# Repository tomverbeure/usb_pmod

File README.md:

# USB Combo PMOD

It's common to implement Full Speed or Low Speed (FS/LS) USB host or device controllers
on an FPGA by just using their digital IOs, configured as 3V3 LVCMOS. 

A good example is the [TinyFPGA BX board](https://www.adafruit.com/product/4038), 
which comes by default with a hardware-only USB device controller that's used to program new bitstreams into flash. 

Another one is [Fomu](https://www.crowdsupply.com/sutajio-kosagi/fomu), another FPGA development
board that's about as tiny as the USB Type-A connector itself.

However, on FPGAs such as those from the MAX10 family, this solution doesn't work: at
3V3, their IOs don't have the required driving strength. (Only 2mA for a 3V3 LVCMOS IO
on a MAX10.)

For those cases, the easiest FS/LS solution is to use an 
[STUSB03E PHY](https://www.st.com/en/interfaces-and-transceivers/stusb03e.html) for USB host or USB device.
It's a tiny little chip that translates regular digital signals as low as 1.6V to 
USB standard compliant signaling levels.

This project is a PMOD compatible module that contains an STUSB03E, 
the necessary passive components around it, as well as a USB Type-A or
USB Type-B connector footprint.

You need to decide up front whether to use PMOD for USB host or device
purposes, and change the soldered components accordingly.

It's a 4-layer PCB which is overkill, but there's currently no cost difference between
2 and 4 layer PCBs at [JLCPCB](https://jlcpcb.com), so I didn't spend any time to make
it work with 2 layers. It's definitely doable though!

## Instructions

Load the project with KiCAD, or check out a PDF of the schematic [here](./usb_combo_pmod_schematic.pdf)

Use a USB Device:

* Populate J4 (USB B connector) and R3 (if LS support required)
* Don't populate: R4, R5, J5 (USB A connector)
* Don't connect the J3-VBUS pin to anything! (The 5V will come from the USB cable.)

Use as USB Host:

* Populate J5, R4, R5
* Don't populate: J4, R3
* Connect the J3-VBUS pin to an external +5V supply

## BOM

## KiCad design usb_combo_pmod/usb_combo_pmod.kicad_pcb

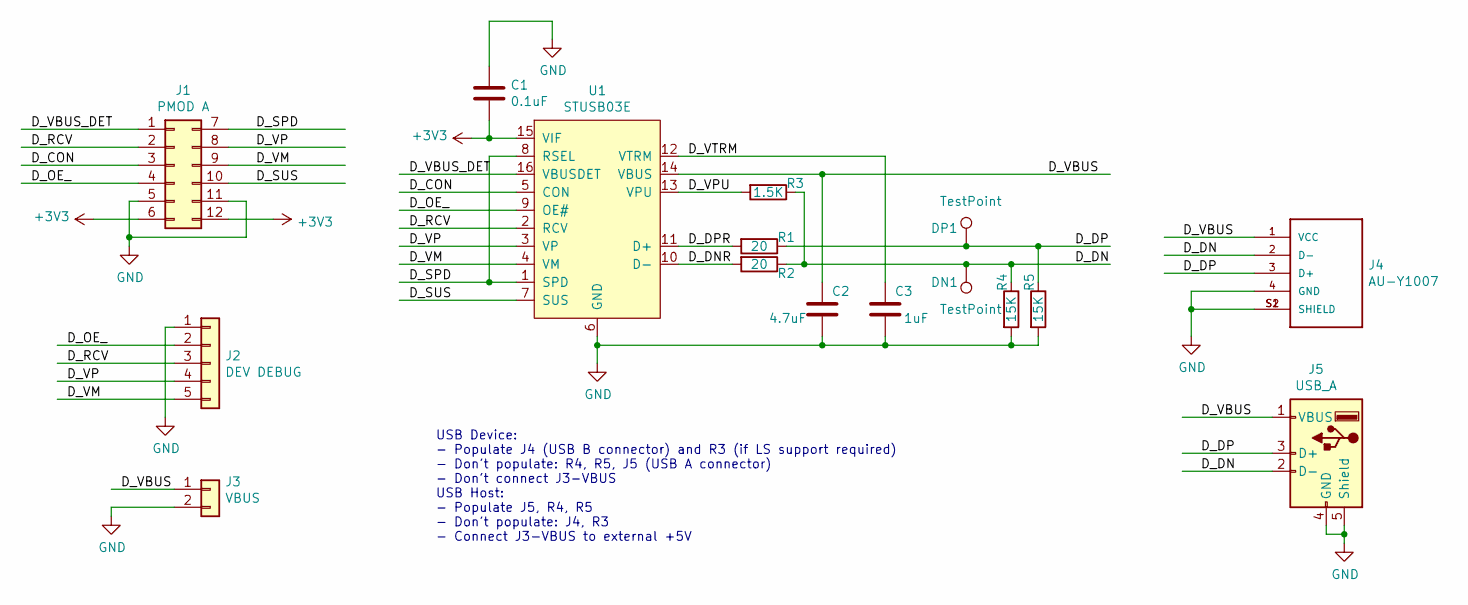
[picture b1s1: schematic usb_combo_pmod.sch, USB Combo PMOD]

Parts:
C1: 0.1uF; C_0603_1608Metric_Pad1.05x0.95mm_HandSolder
C2: 4.7uF; C_0603_1608Metric_Pad1.05x0.95mm_HandSolder
C3: 1uF; C_0603_1608Metric_Pad1.05x0.95mm_HandSolder
DN1: TestPoint; TestPoint_THTPad_1.0x1.0mm_Drill0.5mm
DP1: TestPoint; TestPoint_THTPad_1.0x1.0mm_Drill0.5mm
J1: PMOD A; PMOD_Male
J2: DEV DEBUG; PinHeader_1x05_P2.54mm_Vertical
J3: VBUS; PinHeader_1x02_P2.54mm_Vertical
J4: AU-Y1007; ASSMANN_AU-Y1007
J5: USB_A; USB_A_Stewart_SS-52100-001_Horizontal
R1, R2: 20; R_0603_1608Metric_Pad1.05x0.95mm_HandSolder
R3: 1.5K; R_0603_1608Metric_Pad1.05x0.95mm_HandSolder
R4, R5: 15K; R_0603_1608Metric_Pad1.05x0.95mm_HandSolder
U1: STUSB03E; QFN-16-1EP_3x3mm_P0.5mm_EP1.9x1.9mm

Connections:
+3V3: C1.2, J1.6, J1.12, U1.15 (VIF)
/D_CON: J1.3, U1.5 (CON)
/D_DN: DN1.1, J4.2 (D-), J5.2 (D-), R2.1, R3.1, R4.1
/D_DNR: R2.2, U1.10 (D-)
/D_DP: DP1.1, J4.3 (D+), J5.3 (D+), R1.1, R5.1
/D_DPR: R1.2, U1.11 (D+)
/D_OE_: J1.4, J2.2, U1.9 (OE#)
/D_RCV: J1.2, J2.3, U1.2 (RCV)
/D_SPD: J1.7, U1.1 (SPD), U1.8 (RSEL)
/D_SUS: J1.10, U1.7 (SUS)
/D_VBUS: C2.1, J3.1, J4.1 (VCC), J5.1 (VBUS), U1.14 (VBUS)
/D_VBUS_DET: J1.1, U1.16 (VBUSDET)
/D_VM: J1.9, J2.5, U1.4 (VM)
/D_VP: J1.8, J2.4, U1.3 (VP)
/D_VPU: R3.2, U1.13 (VPU)
/D_VTRM: C3.1, U1.12 (VTRM)
GND: C1.1, C2.2, C3.2, J1.5, J1.11, J2.1, J3.2, J4.4 (GND), J4.S1 (SHIELD), J4.S2 (SHIELD), J5.4 (GND), J5.5 (Shield), R4.2, R5.2, U1.6 (GND)

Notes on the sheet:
USB Device: - Populate J4 (USB B connector) and R3 (if LS support required) - Don't populate: R4, R5, J5 (USB A connector) - Don't connect J3-VBUS USB Host: - Populate J5, R4, R5 - Don't populate: J4, R3 - Connect J3-VBUS to external +5V

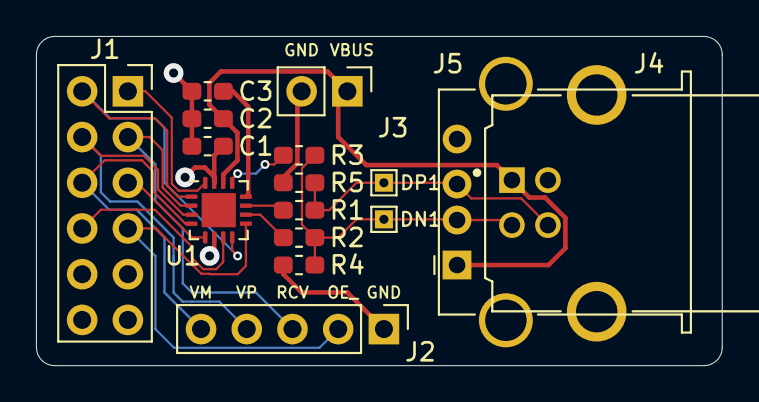
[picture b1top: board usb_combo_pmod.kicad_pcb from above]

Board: 4 copper layers, 38.1 x 18.3 mm, 16 parts (0 on the bottom side), 17 nets.

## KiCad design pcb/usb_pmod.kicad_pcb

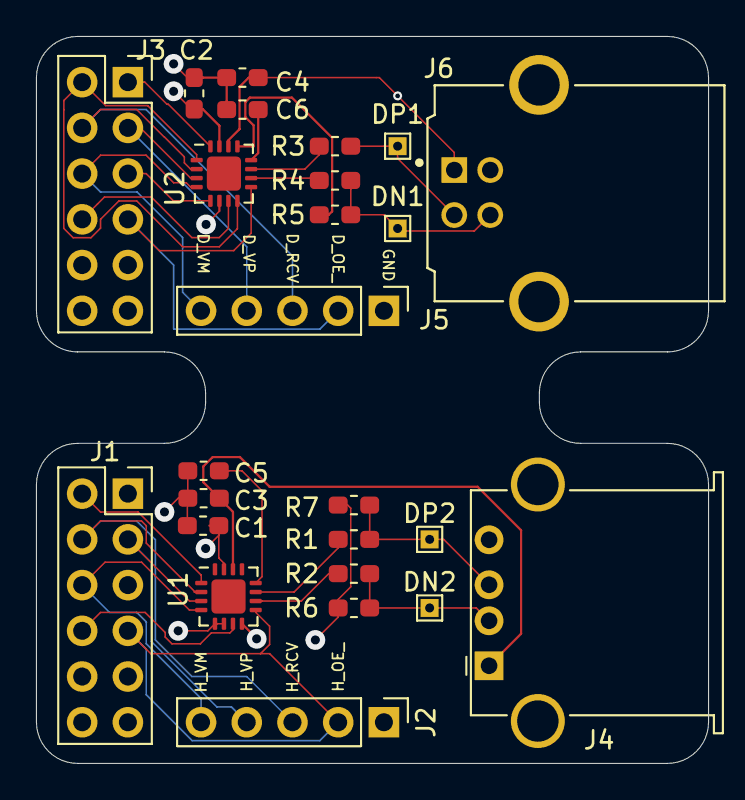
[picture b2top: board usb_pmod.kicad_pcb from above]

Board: 4 copper layers, 37.3 x 40.4 mm, 25 parts (0 on the bottom side), 29 nets.

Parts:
C1, C2: 0.1uF; C_0603_1608Metric_Pad1.05x0.95mm_HandSolder
C3, C4: 4.7uF; C_0603_1608Metric_Pad1.05x0.95mm_HandSolder
C5, C6: 1uF; C_0603_1608Metric_Pad1.05x0.95mm_HandSolder
DN1, DN2: TestPoint; TestPoint_THTPad_1.0x1.0mm_Drill0.5mm
DP1, DP2: TestPoint; TestPoint_THTPad_1.0x1.0mm_Drill0.5mm
J1: PMOD A; PMOD_Male
J2: HOST DEBUG; PinHeader_1x05_P2.54mm_Vertical
J3: PMOD B; PMOD_Male
J4: USB_A; USB_A_Stewart_SS-52100-001_Horizontal
J5: DEV DEBUG; PinHeader_1x05_P2.54mm_Vertical
J6: AU-Y1007; ASSMANN_AU-Y1007
R1, R2, R3, R4: 20; R_0603_1608Metric_Pad1.05x0.95mm_HandSolder
R5: 1.5K; R_0603_1608Metric_Pad1.05x0.95mm_HandSolder
R6, R7: 15K; R_0603_1608Metric_Pad1.05x0.95mm_HandSolder
U1, U2: STUSB03E; QFN-16-1EP_3x3mm_P0.5mm_EP1.9x1.9mm

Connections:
+3V3: C1.2, C2.2, J1.6, J1.12, J3.6, J3.12, U1.15, U2.15
/D_CON: J3.3, U2.5
/D_DN: DN1.1, J6.3, R4.1, R5.1
/D_DNR: R4.2, U2.10
/D_DP: DP1.1, J6.2, R3.1
/D_DPR: R3.2, U2.11
/D_OE_: J3.4, J5.2, U2.9
/D_RCV: J3.8, J5.3, U2.2
/D_SPD: J3.7, U2.1, U2.8
/D_SUS: J3.10, U2.7
/D_VBUS: C4.1, J6.1, U2.14
/D_VBUS_DET: J3.1, U2.16
/D_VM: J3.9, J5.5, U2.4
/D_VP: J3.2, J5.4, U2.3
/D_VPU: R5.2, U2.13
/D_VTRM: C6.1, U2.12
/H_DN: DN2.1, J4.2, R2.1, R6.1
/H_DNR: R2.2, U1.10
/H_DP: DP2.1, J4.3, R1.1, R7.1
/H_DPR: R1.2, U1.11
/H_OE_: J1.4, J2.2, U1.9
/H_RCV: J1.8, J2.3, U1.2
/H_SPD: J1.7, U1.1
/H_SUS: J1.10, U1.7
/H_VBUS: C3.1, J4.1, U1.14
/H_VM: J1.9, J2.5, U1.4
/H_VP: J1.2, J2.4, U1.3
/H_VTRM: C5.1, U1.12
GND: C1.1, C2.1, C3.2, C4.2, C5.2, C6.2, J1.5, J1.11, J2.1, J3.5, J3.11, J4.4, J4.5, J5.1, J6.4, J6.S1, J6.S2, R6.2, R7.2, U1.5, U1.6, U1.8, U2.6

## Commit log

2021-07-01 First version.
2021-07-01 Fix labels.
2021-07-01 Add diagrams.
2021-07-01 Resize image.
2021-07-02 USB Combo PMOD
2021-07-02 Add schematic image.
2021-07-02 More info.
2021-07-02 BOM.

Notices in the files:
usb_combo_pmod/usb_combo_pmod.sch:
License: Unlicense (See unlicense.org)
